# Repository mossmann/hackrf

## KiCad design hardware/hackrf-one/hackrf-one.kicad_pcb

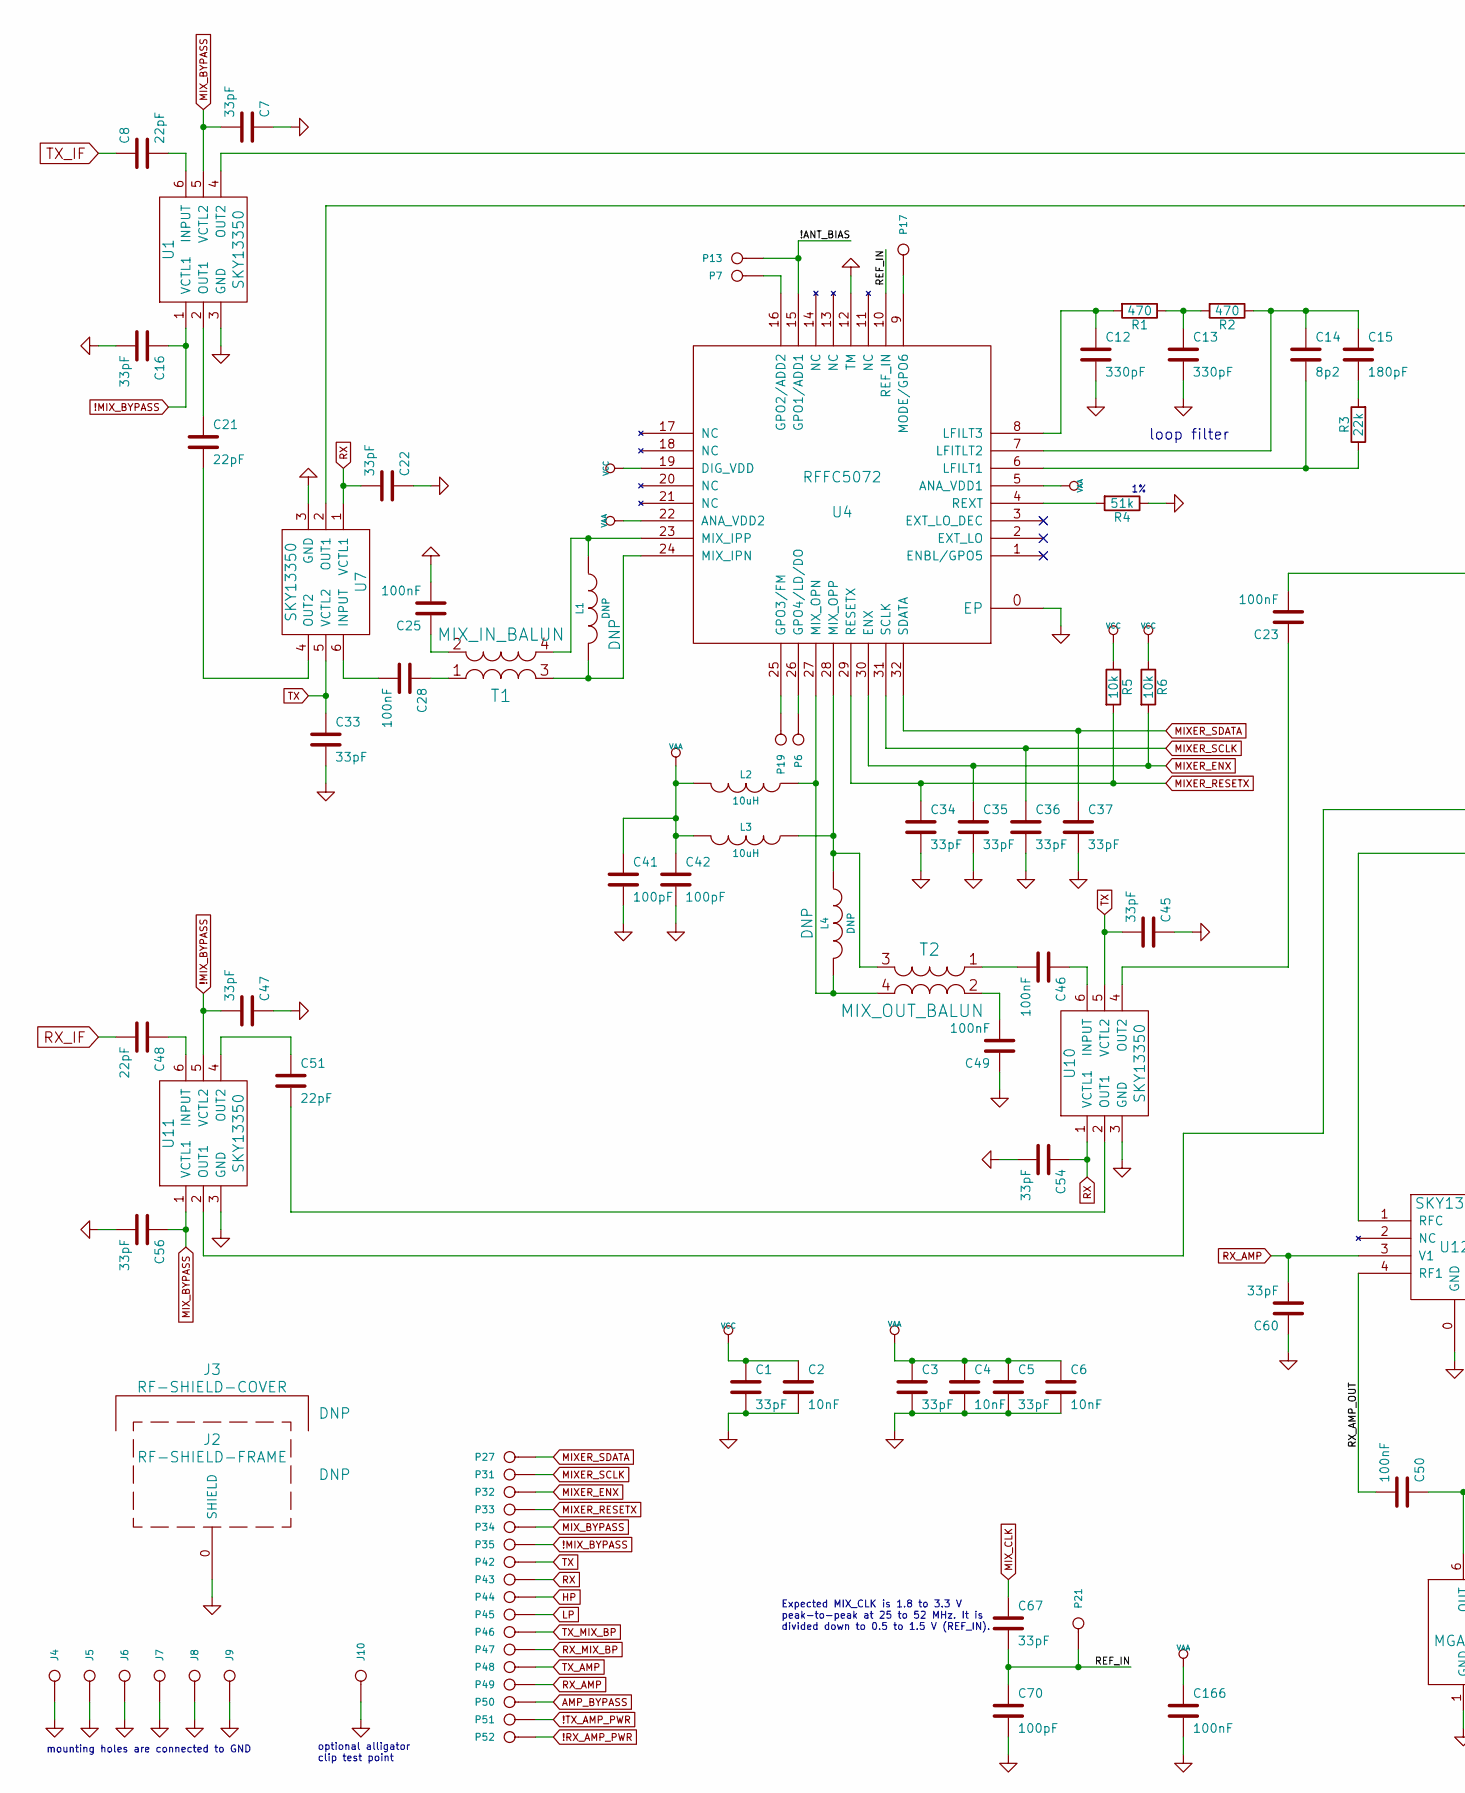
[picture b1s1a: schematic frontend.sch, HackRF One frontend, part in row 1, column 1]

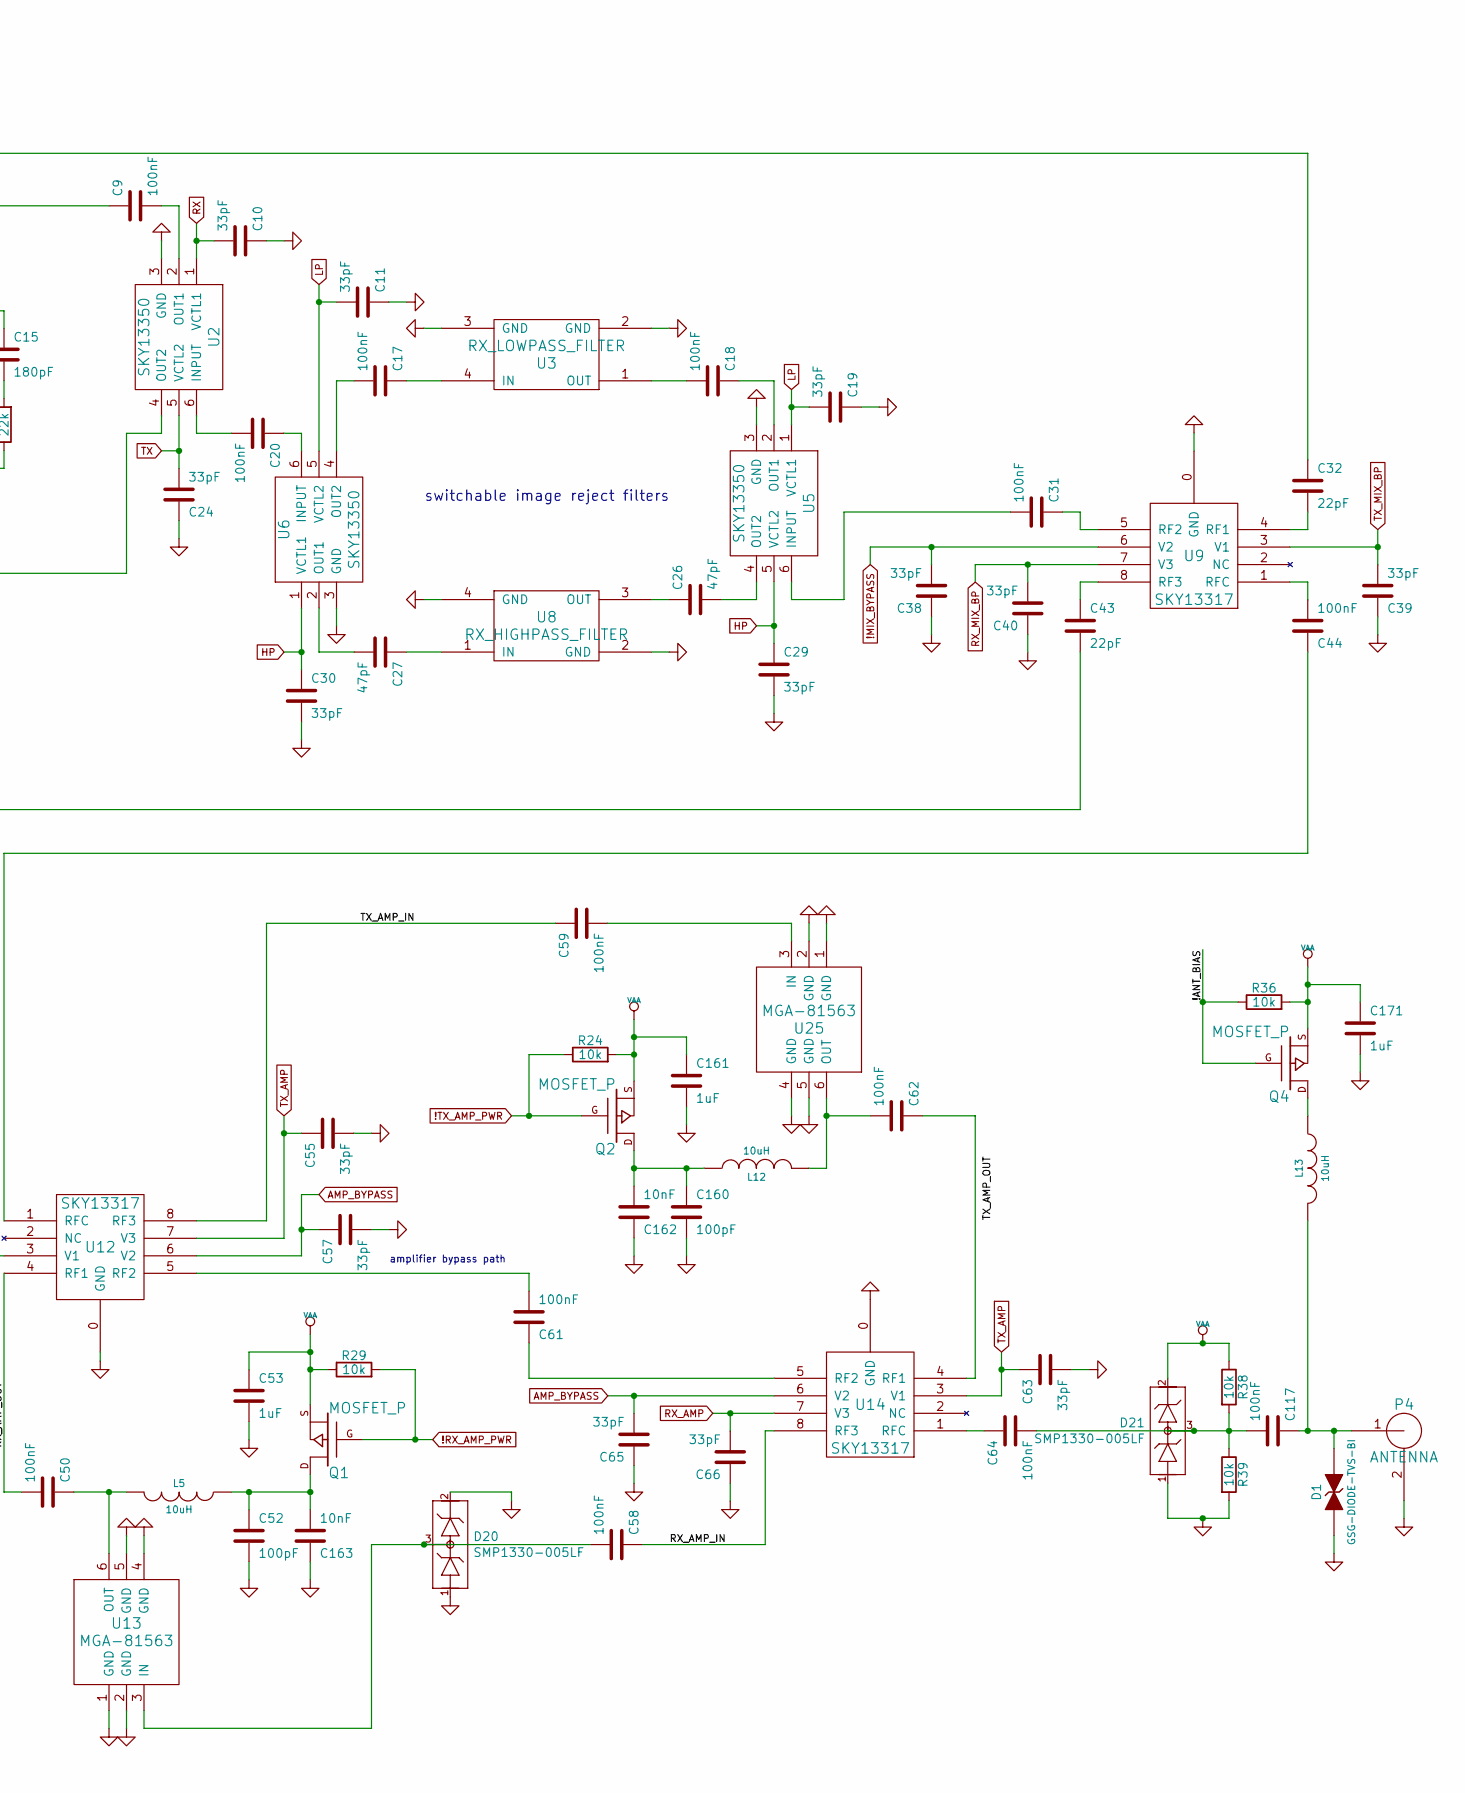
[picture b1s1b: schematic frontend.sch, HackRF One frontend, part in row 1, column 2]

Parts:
C1, C3, C5, C7, C10, C11, C16, C19, C22, C24, C29, C30, C33, C34, C35, C36, C37, C38, C39, C40, C45, C47, C54, C55, C56, C57, C60, C63, C65, C66, C67: 33pF; GSG-0402; Part Number GRM1555C1H330JA01D
C2, C4, C6, C162, C163: 10nF; GSG-0402; Part Number GRM155R71C103KA01D
C8, C21, C32, C43, C48, C51: 22pF; GSG-0402; Part Number GRM1555C1H220JA01D
C9, C17, C18, C20, C23, C25, C28, C31, C44, C46, C49, C50, C58, C59, C61, C62, C64, C117, C166: 100nF; GSG-0402; Part Number GRM155R61A104KA01D
C12, C13: 330pF; GSG-0402; Part Number GRM155R71H331KA01D
C14: 8p2; GSG-0402; Part Number UMK105CG8R2DV-F
C15: 180pF; GSG-0402; Part Number GRM1555C1H181JA01D
C26, C27: 47pF; GSG-0402; Part Number GRM1555C1H470JA01D
C41, C42, C52, C70, C160: 100pF; GSG-0402; Part Number GRM1555C1H101JA01D
C53, C161, C171: 1uF; GSG-0402; Part Number LMK105BJ105KV-F
D1: GSG-DIODE-TVS-BI; GSG-0402; Part Number LXES15AAA1-100
D20, D21: SMP1330-005LF; SOT23-DD
J2: RF-SHIELD-FRAME; GSG-SHIELD-BMI-S-230; Part Number BMI-S-230-F-R
J3: RF-SHIELD-COVER; GSG-NULL-MODULE; Part Number BMI-S-230-C
J4, J5, J6, J7, J8, J9: MOUNTING_HOLE; GSG-HOLE126MIL-COPPER
J10: GND_CLIP; GSG-TEST-POINT-S1751-46R; Part Number S1751-46R
L1, L4: DNP; GSG-0402
L2, L3, L5, L12, L13: 10uH; GSG-0603; Part Number BRL1608T100M
P4: ANTENNA; GSG-SMA-73251-2120; Part Number 73251-2121
P6: GPO4; GSG-TESTPOINT-50MIL
P7: GPO2; GSG-TESTPOINT-50MIL
P13: GPO1; GSG-TESTPOINT-50MIL
P17: GPO6; GSG-TESTPOINT-50MIL
P19: GPO3; GSG-TESTPOINT-50MIL
P21: REF_IN; GSG-TESTPOINT-50MIL
P27: MIXER_SDATA; GSG-TESTPOINT-50MIL
P31: MIXER_SCLK; GSG-TESTPOINT-50MIL
P32: MIXER_ENX; GSG-TESTPOINT-50MIL
P33: MIXER_RESETX; GSG-TESTPOINT-50MIL
P34: MIX_BYPASS; GSG-TESTPOINT-50MIL
P35: !MIX_BYPASS; GSG-TESTPOINT-50MIL
P42: TX; GSG-TESTPOINT-50MIL
P43: RX; GSG-TESTPOINT-50MIL
P44: HP; GSG-TESTPOINT-50MIL
P45: LP; GSG-TESTPOINT-50MIL
P46: TX_MIX_BP; GSG-TESTPOINT-50MIL
P47: RX_MIX_BP; GSG-TESTPOINT-50MIL
P48: TX_AMP; GSG-TESTPOINT-50MIL
P49: RX_AMP; GSG-TESTPOINT-50MIL
P50: AMP_BYPASS; GSG-TESTPOINT-50MIL
P51: !TX_AMP_PWR; GSG-TESTPOINT-50MIL
P52: !RX_AMP_PWR; GSG-TESTPOINT-50MIL
Q1, Q2, Q4: MOSFET_P; SOT23GDS; Part Number BSS84
R1, R2: 470; GSG-0402; Part Number RMCF0402JT470R
R3: 22k; GSG-0402; Part Number ERJ-2GEJ223X
R4: 51k; GSG-0402; Part Number RMCF0402FT51K0
R5, R6, R24, R29, R36, R38, R39: 10k; GSG-0402; Part Number RMCF0402JT10K0
T1: MIX_IN_BALUN; GSG-B0310J50100AHF; Part Number B0310J50100AHF
T2: MIX_OUT_BALUN; GSG-B0310J50100AHF; Part Number B0310J50100AHF
U1, U2, U5, U6, U7, U10, U11: SKY13350; GSG-SKY13350-385LF; Part Number SKY13350-385LF
U3: RX_LOWPASS_FILTER; GSG-LP0603; Part Number LP0603A1880ANTR
U4: RFFC5072; GSG-QFN32; Part Number RFFC5072TR7
U8: RX_HIGHPASS_FILTER; GSG-HP-DEA; Part Number DEA162400HT-8004B1
U9, U12, U14: SKY13317; GSG-SKY13317-373LF; Part Number SKY13317-373LF
U13, U25: MGA-81563; GSG-SOT363; Part Number MGA-81563-TR1G

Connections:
!MIX_BYPASS: C16.1, C38.2, C47.2, P35.1, U1.1 (VCTL1), U9.6 (V2), U11.5 (VCTL2); also elsewhere on the board
!RX_AMP_PWR: P52.1, Q1.G, R29.2; also elsewhere on the board
!TX_AMP_PWR: P51.1, Q2.G, R24.1; also elsewhere on the board
/frontend/!ANT_BIAS: P13.1, Q4.G, R36.1, U4.15 (GPO1/ADD1)
/frontend/REF_IN: C67.2, C70.1, P21.1, U4.10 (REF_IN)
/frontend/RX_AMP_IN: C58.1, U14.8 (RF3)
/frontend/RX_AMP_OUT: C50.2, U12.4 (RF1)
/frontend/TX_AMP_IN: C59.1, U12.8 (RF3)
AMP_BYPASS: C57.1, C65.2, P50.1, U12.6 (V2), U14.6 (V2); also elsewhere on the board
GND: C1.2, C2.2, C3.2, C4.2, C5.2, C6.2, C7.1, C10.1, C11.1, C12.2, C13.2, C16.2, C19.1, C22.1, C24.1, C25.2, C29.2, C30.2, C33.2, C34.2, C35.2, C36.2, C37.2, C38.1, C39.1, C40.1, C41.2, C42.2, C45.1, C47.1, C49.1, C52.2, C53.2, C54.2, C55.2, C56.2, C57.2, C60.1, C63.2, C65.1, C66.1, C70.2, C160.2, C161.2, C162.1, C163.1, C166.2, C171.2, D1.1 (A), D20.1, D20.2, D21.1, J2.0, J4.1, J5.1, J6.1, J7.1, J8.1, J9.1, J10.1, P4.2 (GND), R4.1, R39.2, U1.3 (GND), U2.3 (GND), U3.2 (GND), U3.3 (GND), U4.0 (EP), U4.12 (TM), U5.3 (GND), U6.3 (GND), U7.3 (GND), U8.2 (GND), U8.4 (GND), U9.0 (GND), U10.3 (GND), U11.3 (GND), U12.0 (GND), U13.1 (GND), U13.2 (GND), U13.4 (GND), U13.5 (GND), U14.0 (GND), U25.1 (GND), U25.2 (GND), U25.4 (GND), U25.5 (GND); also elsewhere on the board
HP: C29.1, C30.1, P44.1, U5.5 (VCTL2), U6.1 (VCTL1); also elsewhere on the board
LP: C11.2, C19.2, P45.1, U5.1 (VCTL1), U6.5 (VCTL2); also elsewhere on the board
MIXER_ENX: C35.1, P32.1, R6.2, U4.30 (ENX); also elsewhere on the board
MIXER_RESETX: C34.1, P33.1, R5.2, U4.29 (RESETX); also elsewhere on the board
MIXER_SCLK: C36.1, P31.1, U4.31 (SCLK); also elsewhere on the board
MIXER_SDATA: C37.1, P27.1, U4.32 (SDATA); also elsewhere on the board
MIX_BYPASS: C7.2, C56.1, P34.1, U1.5 (VCTL2), U11.1 (VCTL1); also elsewhere on the board
MIX_CLK: C67.1; also elsewhere on the board
unnamed: C8.2, U1.6 (INPUT)
unnamed: C9.1, U7.2 (OUT1)
unnamed: C9.2, U2.2 (OUT1)
unnamed: C12.1, R1.2, U4.8 (LFILT3)
unnamed: C13.1, R1.1, R2.2
unnamed: C14.1, C15.1, R2.1, U4.7 (LFITLT2)
unnamed: C14.2, R3.1, U4.6 (LFILT1)
unnamed: C15.2, R3.2
unnamed: C17.1, U3.4 (IN)
unnamed: C17.2, U6.4 (OUT2)
unnamed: C18.1, U5.2 (OUT1)
unnamed: C18.2, U3.1 (OUT)
unnamed: C20.1, U6.6 (INPUT)
unnamed: C20.2, U2.6 (INPUT)
unnamed: C21.1, U1.2 (OUT1)
unnamed: C21.2, U7.4 (OUT2)
unnamed: C23.1, U10.4 (OUT2)
unnamed: C23.2, U2.4 (OUT2)
unnamed: C25.1, T1.2 (S2)
unnamed: C26.1, U8.3 (OUT)
unnamed: C26.2, U5.4 (OUT2)
unnamed: C27.1, U8.1 (IN)
unnamed: C27.2, U6.2 (OUT1)
unnamed: C28.1, T1.1 (S1)
unnamed: C28.2, U7.6 (INPUT)
unnamed: C31.1, U9.5 (RF2)
unnamed: C31.2, U5.6 (INPUT)
unnamed: C32.1, U1.4 (OUT2)
unnamed: C32.2, U9.4 (RF1)
unnamed: C43.1, U9.8 (RF3)
unnamed: C43.2, U11.2 (OUT1)
unnamed: C44.1, U12.1 (RFC)
unnamed: C44.2, U9.1 (RFC)
unnamed: C46.1, U10.6 (INPUT)
unnamed: C46.2, T2.1 (S1)
unnamed: C48.1, U11.6 (INPUT)
unnamed: C49.2, T2.2 (S2)
unnamed: C50.1, L5.2, U13.6 (OUT)
unnamed: C51.1, U11.4 (OUT2)
unnamed: C51.2, U10.2 (OUT1)
unnamed: C58.2, D20.3, U13.3 (IN)
unnamed: C59.2, U25.3 (IN)
unnamed: C61.1, U14.5 (RF2)
unnamed: C61.2, U12.5 (RF2)
unnamed: C62.1, U14.4 (RF1)
unnamed: C62.2, L12.2, U25.6 (OUT)
unnamed: C64.1, U14.1 (RFC)
unnamed: C117.1, D1.2 (K), L13.2, P4.1 (RF)
unnamed: C64.2, C117.2, D21.3, R38.2, R39.1
unnamed: C160.1, C162.2, L12.1, Q2.D
unnamed: C52.1, C163.2, L5.1, Q1.D
unnamed: L1.1, T1.4 (PR2), U4.23 (MIX_IPP)
unnamed: L1.2, T1.3 (PR1), U4.24 (MIX_IPN)
unnamed: L2.1, L4.2, T2.4 (PR2), U4.27 (MIX_OPN)
unnamed: L3.1, L4.1, T2.3 (PR1), U4.28 (MIX_OPP)
unnamed: L13.1, Q4.D
unnamed: P6.1, U4.26 (GPO4/LD/DO)
unnamed: P7.1, U4.16 (GPO2/ADD2)
unnamed: P17.1, U4.9 (MODE/GPO6)
unnamed: P19.1, U4.25 (GPO3/FM)
unnamed: R4.2, U4.4 (REXT)
RX: C10.2, C22.2, C54.1, P43.1, U2.1 (VCTL1), U7.1 (VCTL1), U10.1 (VCTL1); also elsewhere on the board
RX_AMP: C60.2, C66.2, P49.1, U12.3 (V1), U14.7 (V3); also elsewhere on the board
RX_IF: C48.2; also elsewhere on the board
RX_MIX_BP: C40.2, P47.1, U9.7 (V3); also elsewhere on the board
TX: C24.2, C33.1, C45.2, P42.1, U2.5 (VCTL2), U7.5 (VCTL2), U10.5 (VCTL2); also elsewhere on the board
TX_AMP: C55.1, C63.1, P48.1, U12.7 (V3), U14.3 (V1); also elsewhere on the board
TX_IF: C8.1; also elsewhere on the board
TX_MIX_BP: C39.2, P46.1, U9.3 (V1); also elsewhere on the board
VAA: C3.1, C4.1, C5.1, C6.1, C41.1, C42.1, C53.1, C161.1, C166.1, C171.1, D21.2, L2.2, L3.2, Q1.S, Q2.S, Q4.S, R24.2, R29.1, R36.2, R38.1, U4.5 (ANA_VDD1), U4.22 (ANA_VDD2); also elsewhere on the board
VCC: C1.1, C2.1, R5.1, R6.1, U4.19 (DIG_VDD); also elsewhere on the board

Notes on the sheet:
amplifier bypass path
switchable image reject filters
Expected MIX_CLK is 1.8 to 3.3 V peak-to-peak at 25 to 52 MHz. It is divided down to 0.5 to 1.5 V (REF_IN).
loop filter
mounting holes are connected to GND
optional alligator clip test point

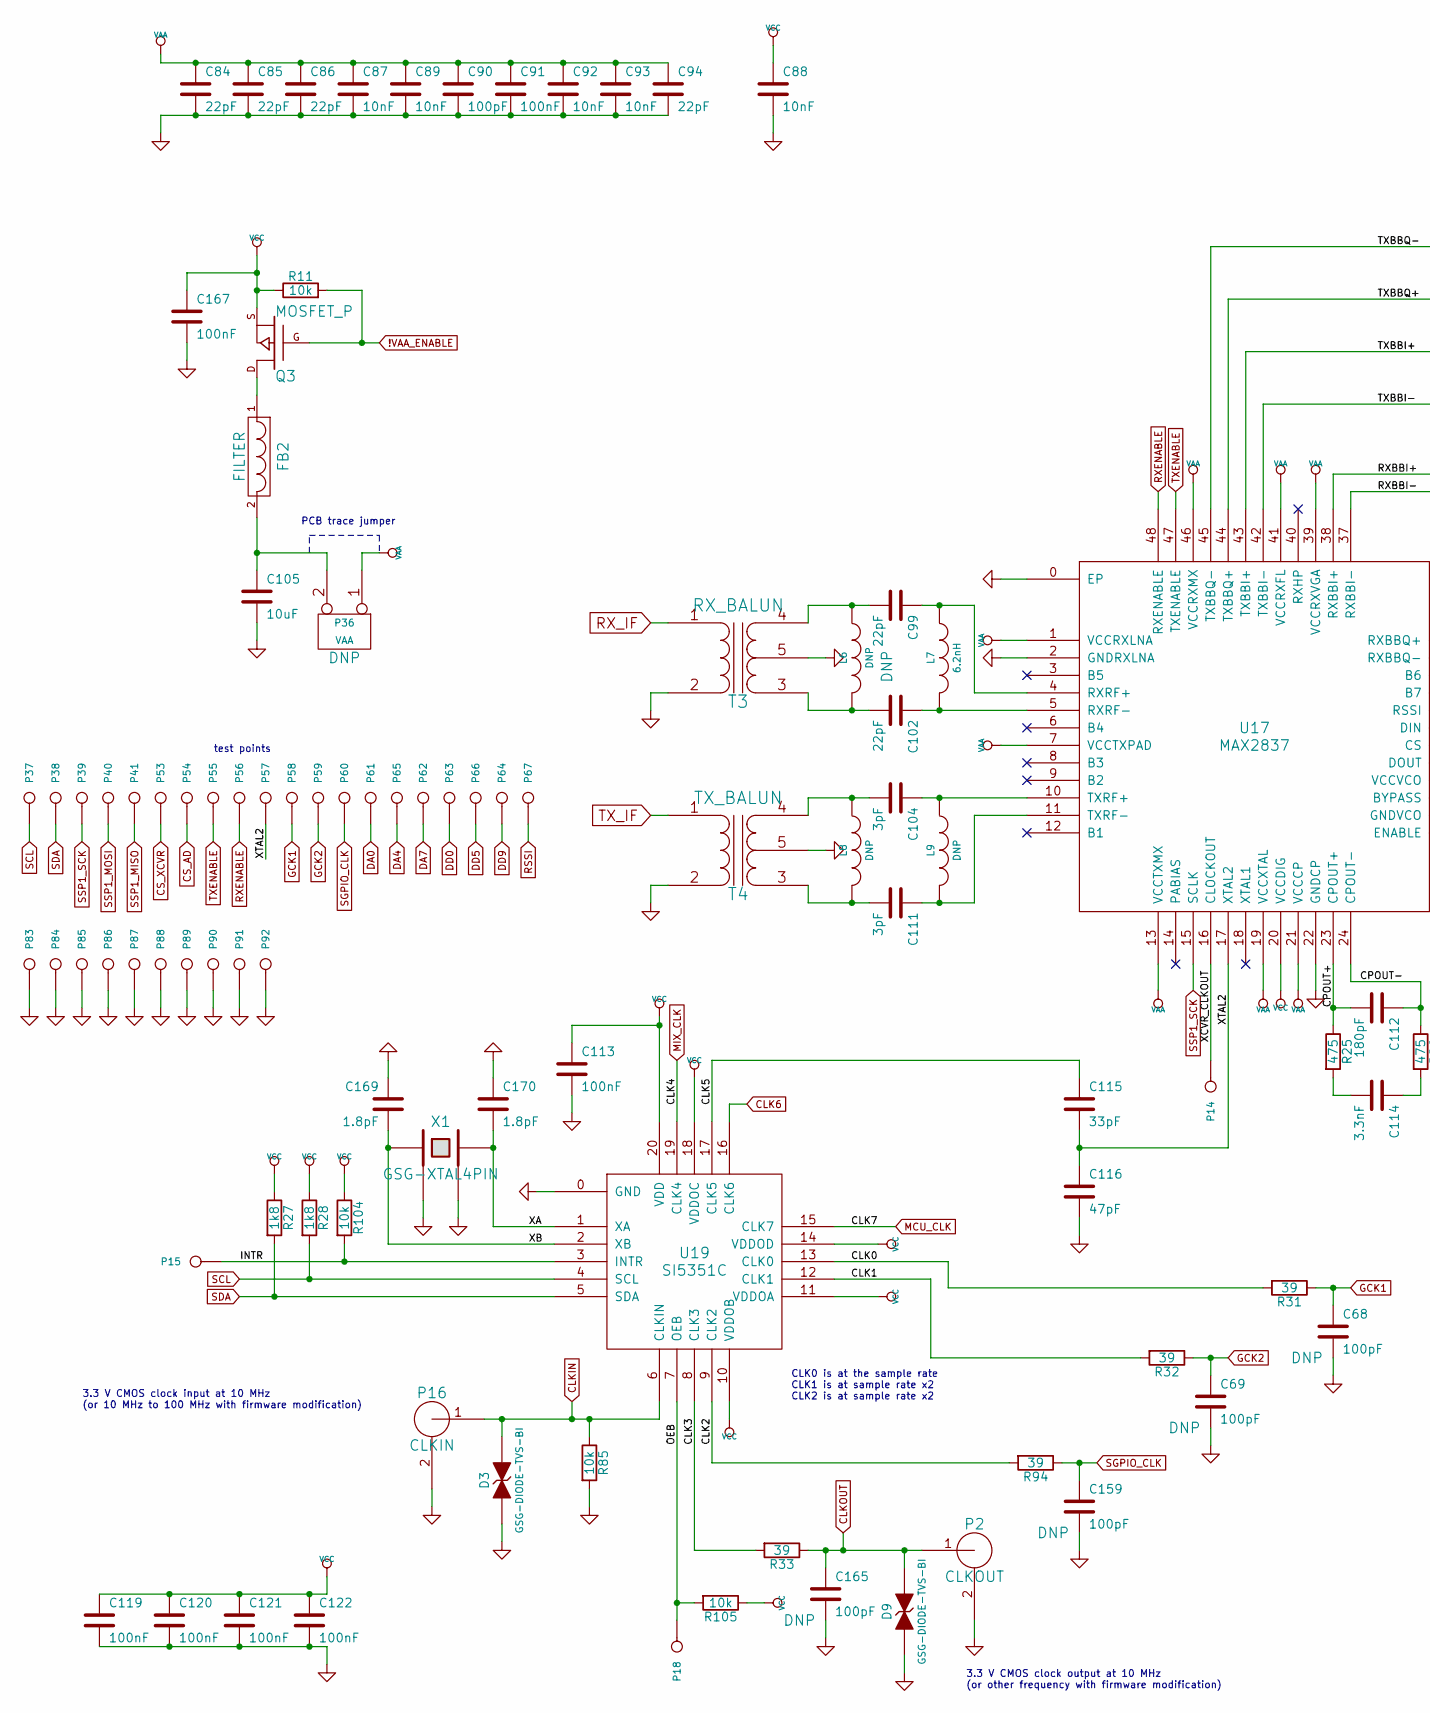
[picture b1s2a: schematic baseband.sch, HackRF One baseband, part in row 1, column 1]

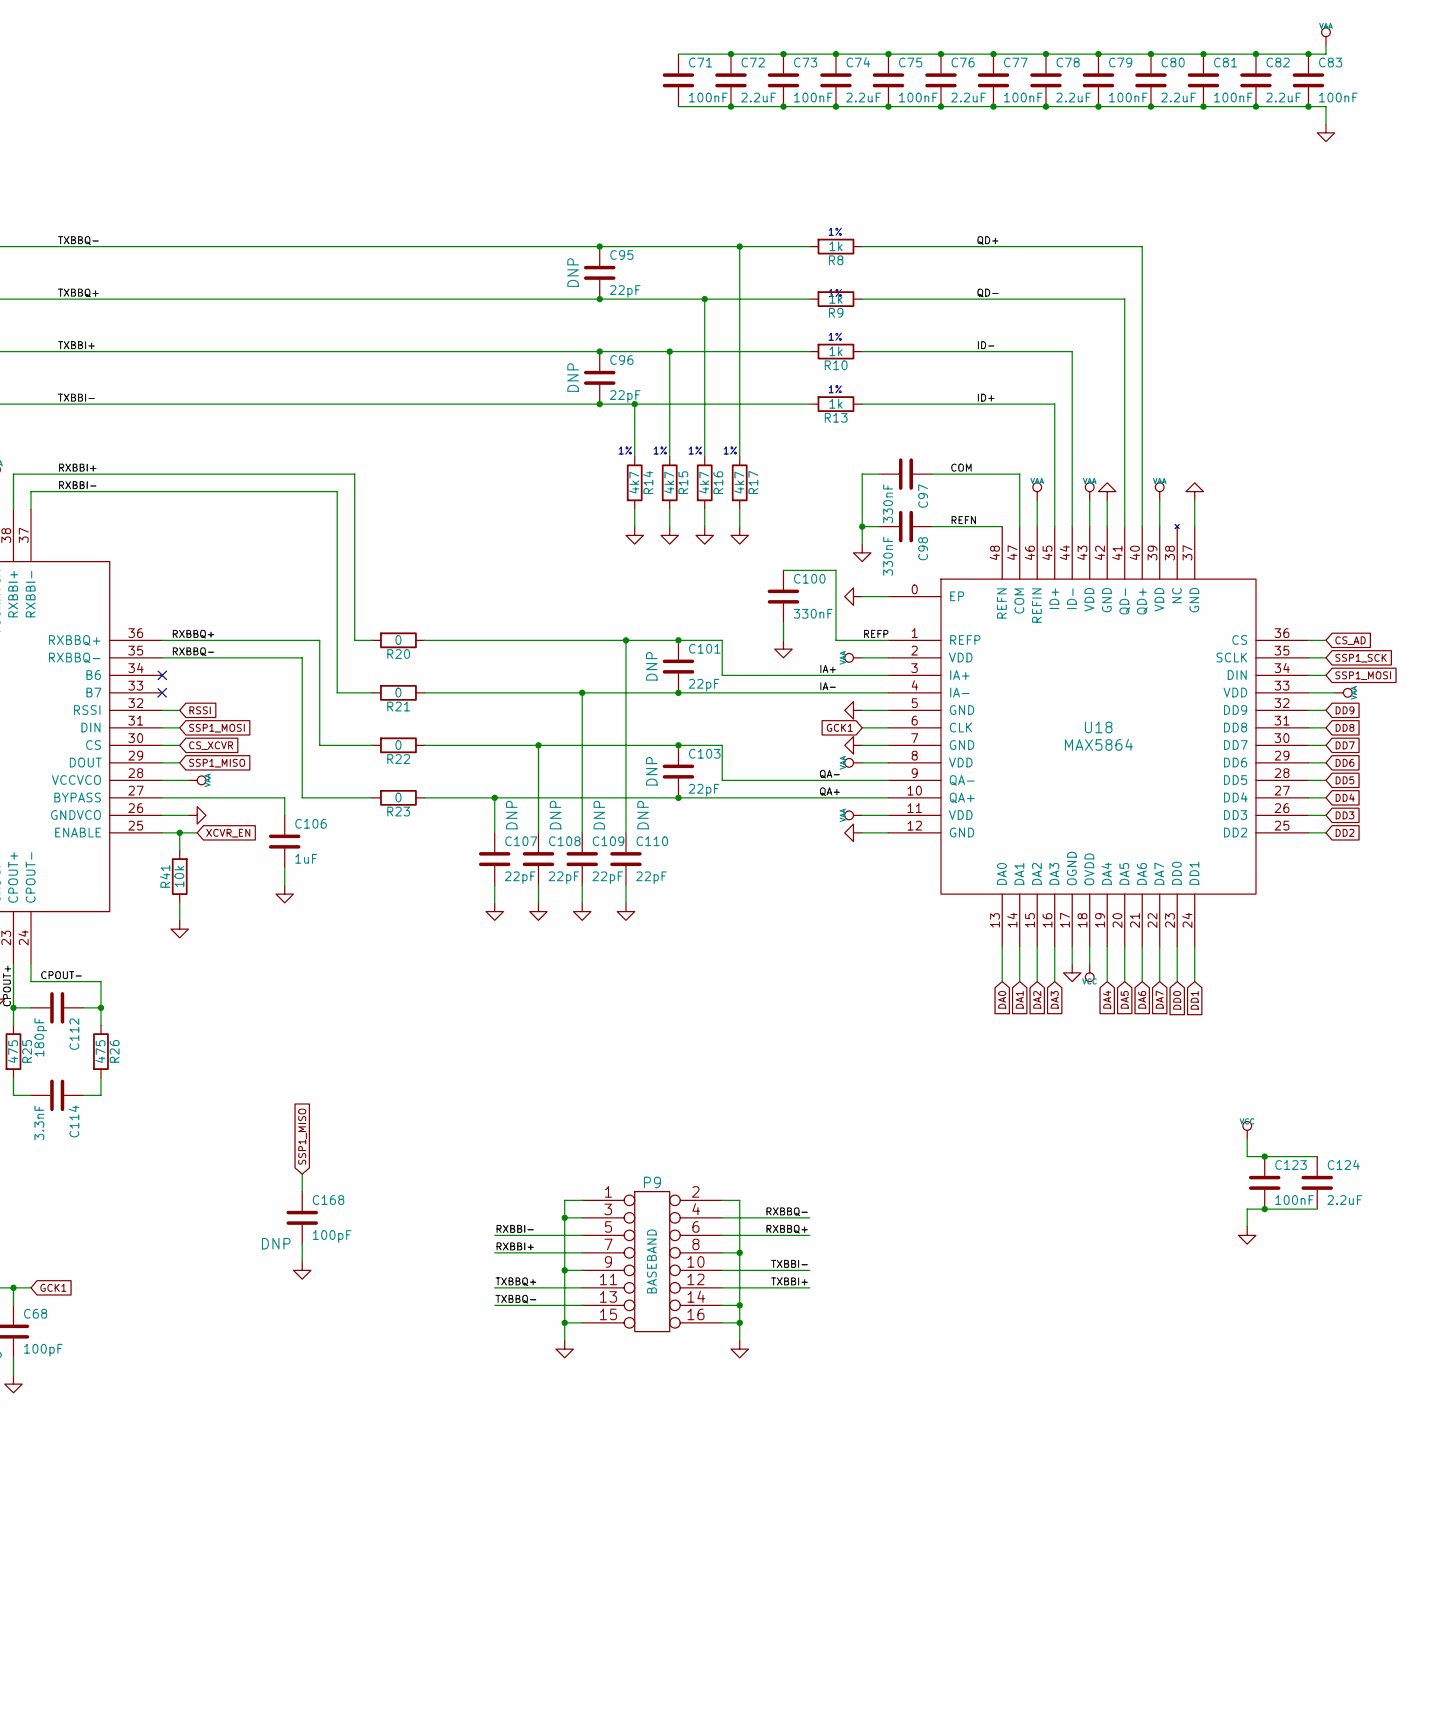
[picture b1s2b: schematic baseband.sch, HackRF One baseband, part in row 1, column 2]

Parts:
C68, C69, C90, C159, C165, C168: 100pF; GSG-0402; Part Number GRM1555C1H101JA01D
C71, C73, C75, C77, C79, C81, C83, C91, C113, C119, C120, C121, C122, C123, C167: 100nF; GSG-0402; Part Number GRM155R61A104KA01D
C72, C74, C76, C78, C80, C82, C124: 2.2uF; GSG-0402; Part Number LMK105BJ225MV-F
C84, C85, C86, C94, C95, C96, C99, C101, C102, C103, C107, C108, C109, C110: 22pF; GSG-0402; Part Number GRM1555C1H220JA01D
C87, C88, C89, C92, C93: 10nF; GSG-0402; Part Number GRM155R71C103KA01D
C97, C98, C100: 330nF; GSG-0402; Part Number GRM155R61A334KE15D
C104, C111: 3pF; GSG-0402; Part Number GRM1555C1H3R0CA01D
C105: 10uF; GSG-0805; Part Number GRM21BR61A106KE19L
C106: 1uF; GSG-0402; Part Number LMK105BJ105KV-F
C112: 180pF; GSG-0402; Part Number GRM1555C1H181JA01D
C114: 3.3nF; GSG-0402; Part Number GRM155R71H332KA01D
C115: 33pF; GSG-0402; Part Number GRM1555C1H330JA01D
C116: 47pF; GSG-0402; Part Number GRM1555C1H470JA01D
C169, C170: 1.8pF; GSG-0402; Part Number GRM1555C1E1R8BA01D
D3, D9: GSG-DIODE-TVS-BI; GSG-0402; Part Number LXES15AAA1-100
FB2: FILTER; GSG-0805; Part Number BLM21PG221SN1D
L6, L8, L9: DNP; GSG-0402
L7: 6.2nH; GSG-0402; Part Number HK10056N2S-T
P2: CLKOUT; GSG-SMA-73251-2120; Part Number 73251-2121
P9: BASEBAND; GSG-HEADER-2x8; Part Number PPPC082LFBN-RC
P14: XCVR_CLKOUT; GSG-TESTPOINT-50MIL
P15: INTR; GSG-TESTPOINT-50MIL
P16: CLKIN; GSG-SMA-73251-2120; Part Number 73251-2121
P18: OEB; GSG-TESTPOINT-50MIL
P36: VAA; GSG-HEADER-1x2
P37: SCL; GSG-TESTPOINT-50MIL
P38: SDA; GSG-TESTPOINT-50MIL
P39: SSP1_SCK; GSG-TESTPOINT-50MIL
P40: SSP1_MOSI; GSG-TESTPOINT-50MIL
P41: SSP1_MISO; GSG-TESTPOINT-50MIL
P53: CS_XCVR; GSG-TESTPOINT-50MIL
P54: CS_AD; GSG-TESTPOINT-50MIL
P55: TXENABLE; GSG-TESTPOINT-50MIL
P56: RXENABLE; GSG-TESTPOINT-50MIL
P57: XTAL2; GSG-TESTPOINT-50MIL
P58: GCK1; GSG-TESTPOINT-50MIL
P59: GCK2; GSG-TESTPOINT-50MIL
P60: SGPIO_CLK; GSG-TESTPOINT-50MIL
P61: DA0; GSG-TESTPOINT-50MIL
P62: DA7; GSG-TESTPOINT-50MIL
P63: DD0; GSG-TESTPOINT-50MIL
P64: DD9; GSG-TESTPOINT-50MIL
P65: DA4; GSG-TESTPOINT-50MIL
P66: DD5; GSG-TESTPOINT-50MIL
P67: RSSI; GSG-TESTPOINT-50MIL
P83, P84, P85, P86, P87, P88, P89, P90, P91, P92: GND; GSG-TESTPOINT-50MIL
Q3: MOSFET_P; SOT23GDS; Part Number DMP2305U-7
R8, R9, R10, R13: 1k; GSG-0402; Part Number RMCF0402FT1K00
R11, R41, R85, R104, R105: 10k; GSG-0402; Part Number RMCF0402JT10K0
R14, R15, R16, R17: 4k7; GSG-0402; Part Number RMCF0402FT4K70
R20, R21, R22, R23: 0; GSG-0402; Part Number RMCF0402ZT0R00
R25, R26: 475; GSG-0402; Part Number RMCF0402JT470R
R27, R28: 1k8; GSG-0402; Part Number RMCF0402JT1K80
R31, R32, R33, R94: 39; GSG-0402; Part Number RMCF0402JT39R0
T3: RX_BALUN; GSG-2500BL14M100; Part Number 2500BL14M100T
T4: TX_BALUN; GSG-2500BL14M100; Part Number 2500BL14M100T
U17: MAX2837; GSG-QFN48-6; Part Number MAX2837ETM+
U18: MAX5864; GSG-QFN48-7; Part Number MAX5864ETM+
U19: SI5351C; GSG-QFN20-4; Part Number SI5351C-B-GM
X1: GSG-XTAL4PIN; GSG-XTAL3.2x2.5mm; Part Number ABM8-25.000MHZ-10-D1G-T

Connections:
!VAA_ENABLE: Q3.G, R11.2; also elsewhere on the board
/baseband/CLK0: R31.2, U19.13 (CLK0)
/baseband/CLK1: R32.2, U19.12 (CLK1)
/baseband/CLK2: R94.2, U19.9 (CLK2)
/baseband/CLK3: R33.2, U19.8 (CLK3)
/baseband/CLK5: C115.1, U19.17 (CLK5)
/baseband/COM: C97.1, U18.47 (COM)
/baseband/CPOUT+: C112.2, R25.1, U17.23 (CPOUT+)
/baseband/CPOUT-: C112.1, R26.1, U17.24 (CPOUT-)
/baseband/IA+: C101.1, C110.1, R20.1, U18.3 (IA+)
/baseband/IA-: C101.2, C109.1, R21.1, U18.4 (IA-)
/baseband/ID+: R13.1, U18.45 (ID+)
/baseband/ID-: R10.1, U18.44 (ID-)
/baseband/INTR: P15.1, R104.2, U19.3 (INTR)
/baseband/OEB: P18.1, R105.2, U19.7 (OEB)
/baseband/QA+: C103.2, C107.1, R23.1, U18.10 (QA+)
/baseband/QA-: C103.1, C108.1, R22.1, U18.9 (QA-)
/baseband/QD+: R8.1, U18.40 (QD+)
/baseband/QD-: R9.1, U18.41 (QD-)
/baseband/REFN: C98.1, U18.48 (REFN)
/baseband/REFP: C100.1, U18.1 (REFP)
/baseband/RXBBI+: P9.7, R20.2, U17.38 (RXBBI+)
/baseband/RXBBI-: P9.5, R21.2, U17.37 (RXBBI-)
/baseband/RXBBQ+: P9.6, R22.2, U17.36 (RXBBQ+)
/baseband/RXBBQ-: P9.4, R23.2, U17.35 (RXBBQ-)
/baseband/TXBBI+: C96.1, P9.12, R10.2, R15.1, U17.43 (TXBBI+)
/baseband/TXBBI-: C96.2, P9.10, R13.2, R14.1, U17.42 (TXBBI-)
/baseband/TXBBQ+: C95.2, P9.11, R9.2, R16.1, U17.44 (TXBBQ+)
/baseband/TXBBQ-: C95.1, P9.13, R8.2, R17.1, U17.45 (TXBBQ-)
/baseband/XA: C170.2, U19.1 (XA), X1.3
/baseband/XB: C169.2, U19.2 (XB), X1.1
/baseband/XCVR_CLKOUT: P14.1, U17.16 (CLOCKOUT)
/baseband/XTAL2: C115.2, C116.1, P57.1, U17.17 (XTAL2)
CLK6: U19.16 (CLK6); also elsewhere on the board
CLKIN: D3.2 (K), P16.1 (RF), R85.1, U19.6 (CLKIN); also elsewhere on the board
CLKOUT: C165.1, D9.2 (K), P2.1 (RF), R33.1; also elsewhere on the board
CS_AD: P54.1, U18.36 (CS); also elsewhere on the board
CS_XCVR: P53.1, U17.30 (CS); also elsewhere on the board
DA0: P61.1, U18.13 (DA0); also elsewhere on the board
DA1: U18.14 (DA1); also elsewhere on the board
DA2: U18.15 (DA2); also elsewhere on the board
DA3: U18.16 (DA3); also elsewhere on the board
DA4: P65.1, U18.19 (DA4); also elsewhere on the board
DA5: U18.20 (DA5); also elsewhere on the board
DA6: U18.21 (DA6); also elsewhere on the board
DA7: P62.1, U18.22 (DA7); also elsewhere on the board
DD0: P63.1, U18.23 (DD0); also elsewhere on the board
DD1: U18.24 (DD1); also elsewhere on the board
DD2: U18.25 (DD2); also elsewhere on the board
DD3: U18.26 (DD3); also elsewhere on the board
DD4: U18.27 (DD4); also elsewhere on the board
DD5: P66.1, U18.28 (DD5); also elsewhere on the board
DD6: U18.29 (DD6); also elsewhere on the board
DD7: U18.30 (DD7); also elsewhere on the board
DD8: U18.31 (DD8); also elsewhere on the board
DD9: P64.1, U18.32 (DD9); also elsewhere on the board
GCK1: C68.1, P58.1, R31.1, U18.6 (CLK); also elsewhere on the board
GCK2: C69.1, P59.1, R32.1; also elsewhere on the board
GND: C68.2, C69.2, C71.2, C72.2, C73.2, C74.2, C75.2, C76.2, C77.2, C78.2, C79.2, C80.2, C81.2, C82.2, C83.2, C84.2, C85.2, C86.2, C87.2, C88.2, C89.2, C90.2, C91.2, C92.2, C93.2, C94.2, C97.2, C98.2, C100.2, C105.2, C106.2, C107.2, C108.2, C109.2, C110.2, C113.2, C116.2, C119.2, C120.2, C121.2, C122.2, C123.2, C124.2, C159.2, C165.2, C167.2, C168.2, C169.1, C170.1, D3.1 (A), D9.1 (A), P2.2 (GND), P9.1, P9.2, P9.3, P9.8, P9.9, P9.14, P9.15, P9.16, P16.2 (GND), P83.1, P84.1, P85.1, P86.1, P87.1, P88.1, P89.1, P90.1, P91.1, P92.1, R14.2, R15.2, R16.2, R17.2, R41.1, R85.2, T3.2 (S2), T3.5 (PM), T4.2 (S2), T4.5 (PM), U17.0 (EP), U17.2 (GNDRXLNA), U17.22 (GNDCP), U17.26 (GNDVCO), U18.0 (EP), U18.5 (GND), U18.7 (GND), U18.12 (GND), U18.17 (OGND), U18.37 (GND), U18.42 (GND), U19.0 (GND), X1.2, X1.4; also elsewhere on the board
MCU_CLK: U19.15 (CLK7); also elsewhere on the board
MIX_CLK: U19.19 (CLK4); also elsewhere on the board
unnamed: C99.1, L7.1, U17.4 (RXRF+)
unnamed: C99.2, L6.1, T3.4 (PR2)
unnamed: C102.1, L7.2, U17.5 (RXRF-)
unnamed: C102.2, L6.2, T3.3 (PR1)
unnamed: C104.1, L9.1, U17.10 (TXRF+)
unnamed: C104.2, L8.1, T4.4 (PR2)
unnamed: C105.1, FB2.2, P36.2 (PM)
unnamed: C106.1, U17.27 (BYPASS)
unnamed: C111.1, L9.2, U17.11 (TXRF-)
unnamed: C111.2, L8.2, T4.3 (PR1)
unnamed: C114.1, R26.2
unnamed: C114.2, R25.2
unnamed: FB2.1, Q3.D
RSSI: P67.1, U17.32 (RSSI); also elsewhere on the board
RXENABLE: P56.1, U17.48 (RXENABLE); also elsewhere on the board
RX_IF: T3.1 (S1); also elsewhere on the board
SCL: P37.1, R28.2, U19.4 (SCL); also elsewhere on the board
SDA: P38.1, R27.2, U19.5 (SDA); also elsewhere on the board
SGPIO_CLK: C159.1, P60.1, R94.1; also elsewhere on the board
SSP1_MISO: C168.1, P41.1, U17.29 (DOUT); also elsewhere on the board
SSP1_MOSI: P40.1, U17.31 (DIN), U18.34 (DIN); also elsewhere on the board
SSP1_SCK: P39.1, U17.15 (SCLK), U18.35 (SCLK); also elsewhere on the board
TXENABLE: P55.1, U17.47 (TXENABLE); also elsewhere on the board
TX_IF: T4.1 (S1); also elsewhere on the board
VAA: C71.1, C72.1, C73.1, C74.1, C75.1, C76.1, C77.1, C78.1, C79.1, C80.1, C81.1, C82.1, C83.1, C84.1, C85.1, C86.1, C87.1, C89.1, C90.1, C91.1, C92.1, C93.1, C94.1, P36.1, U17.1 (VCCRXLNA), U17.7 (VCCTXPAD), U17.13 (VCCTXMX), U17.19 (VCCXTAL), U17.21 (VCCCP), U17.28 (VCCVCO), U17.39 (VCCRXVGA), U17.41 (VCCRXFL), U17.46 (VCCRXMX), U18.2 (VDD), U18.8 (VDD), U18.11 (VDD), U18.33 (VDD), U18.39 (VDD), U18.43 (VDD), U18.46 (REFIN); also elsewhere on the board
VCC: C88.1, C113.1, C119.1, C120.1, C121.1, C122.1, C123.1, C124.1, C167.1, Q3.S, R11.1, R27.1, R28.1, R104.1, R105.1, U17.20 (VCCDIG), U18.18 (OVDD), U19.10 (VDDOB), U19.11 (VDDOA), U19.14 (VDDOD), U19.18 (VDDOC), U19.20 (VDD); also elsewhere on the board
XCVR_EN: R41.2, U17.25 (ENABLE); also elsewhere on the board

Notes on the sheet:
3.3 V CMOS clock output at 10 MHz (or other frequency with firmware modification)
3.3 V CMOS clock input at 10 MHz (or 10 MHz to 100 MHz with firmware modification)
test points
CLK0 is at the sample rate CLK1 is at sample rate x2 CLK2 is at sample rate x2
PCB trace jumper

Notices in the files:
firmware/common/hackrf_core.c:
Copyright 2012 Michael Ossmann <mike@ossmann.com>
Copyright 2012 Jared Boone <jared@sharebrained.com>
Copyright 2013 Benjamin Vernoux <titanmkd@gmail.com>
This program is free software; you can redistribute it and/or modify
it under the terms of the GNU General Public License as published by
the Free Software Foundation; either version 2, or (at your option)
firmware/common/hackrf_core.h:
Copyright 2012 Benjamin Vernoux <titanmkd@gmail.com>
hardware/hackrf-one/baseband.sch:
Copyright 2012-2018 Michael Ossmann
License: GPL v2
